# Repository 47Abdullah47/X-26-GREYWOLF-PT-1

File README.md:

<h1 align="center">﷽</h1>
<h1 align="center">
<font size="48"><b>🛦 X-26 GREYWOLF PT-1</b></font>
</h1><br>

<h4 align="center">
  <b>An experimental prototype of <i>X-26 GREYWOLF</i></b>
</h4>
<p align="center">
<a href="#brief interview of the ">Brief interview of The WOLF</a>•
  <a href="#visual looks">Visual Look</a>•
  <a href="#materials list">Materials List</a>•
  <a href="#electronics list">Electronics List</a>•
<a href="#credits">Credits</a>•
<a href="#license">License</a>
</p>
<br>

> **Status:** PT-1 finished  
> **Design:** Fusion 360  
> **Platform:** [Hack Club Blueprint](https://blueprint.hackclub.com/projects/2458) <br>
> **Total Time Spent:** 3+ years <br>
> **Time spent on Blueprint:** 70+ hrs <br>

---<br>

 <br><br>                        
                        
## Brief Interview Of THE WOLF🐺

This WOLF, not a literal one, is the first PT(prototype) of the experimental plane series **GREY WOLF** 
The PT-1 is single engine (not a literal engine could be in future)powered ,running about **1.3-1.5**meters long ,standing almost **30 cm**tall . 
The WOLF has a wingspan of almost **a meter** and a wing area of a **meter** too. Has a total of **8 control surfaces** Two of 'em are flaps,two ailerons ,two stabilators, and two rudders ,not rudders but whole moving tails.Also features three landing gears all of 'em with openning and closing bays.Also in this prototype i've designed my own type of somewhat lookin like S-duct ,Just to study the effects of air in turbulence while flying at low altitudes at high speeds.Expected speeds are like 150-250 mph ,result of edfs 3.4-4kg thrust and planes empty weight being 1.5-2 kgs ,looks a big number but thats a rough guess and the weight can be reduced in real life development.
Abt the electronics , the budget was going very high above 400$ so, i've decided to build them separately.<br>
*Also the .f3d file is very massive upto 150mb's so i've given a google drive link in the **SOURCE FILE*** <a href="Source files">Link to the source file </a>
<br><br>

## Visual Looks

<br><br>
## Materials List
The list of materials used is as follows:-
- **DEPRON** for surface covering and making inner supports maybe.
- **CARBONFIBRE** for making spars,ribs,and frames which are going to handle some aerodynamic stress.
- **PLYWOOD** supplementary material in case of not usin the carbon fibre. maybe i wont use this.
<br><br>
## Electronics List🔌
The list of electronics used are:-
- **Sg-90 Servo** 180 degree rotating servo, for gaining control over control surfaces.
- **80mm Edf**  The power unit thats gonna powerup the whole jet.
- **22.2v 6000mah Lipo**for running these heavy electronics.
- **Small LED lights** for night flight and night landing purpose
***NOTE:-***other electronics and their firmwares are included in their respective repos
<br><br>
**📣AN IMPORTANT NOTICE**<br>
                         Many of the viewers may resemble it with **F-35**or**F-22**, but its not, Its a blend of **F-35,F-22&F-16**
                         u may find some parts similar, but lemme tell u if u look at the intakes they are similar to F-22's ,
                         If u look at the vertical tails and engine u'll find them similar to F-35,And If someone may look at
                         The airframes they are enhanced form of F-16's Air frames.
                         Therefore please do not mix it with Any other Aircraft,I shall be thankful to u.

## Credits💼📜
First of all I'm gonna Credit my **Father** he taught me almost everything about the aircrafts
He's a professional in his feild ,and He is the who encouraged me to build this project..

Secondly My **Big Bro** he was the atual reason i built it ,cuz he challenged me to make my own one
And hes the one who told me about **Blueprint**.So if he wouldnt have challenged me ,my mind  wouldnt have accelerated those ideas that 
led me to design this beast.

Thirdly **Hackclub Blueprint**
I wanna thank the team for starting this type of projects ,that enables many teenagers to enhance thier skills
Also because of **Blueprint** the project that was only a cad file ,is going to come to life.

## License🔐

CC-BY-4.0

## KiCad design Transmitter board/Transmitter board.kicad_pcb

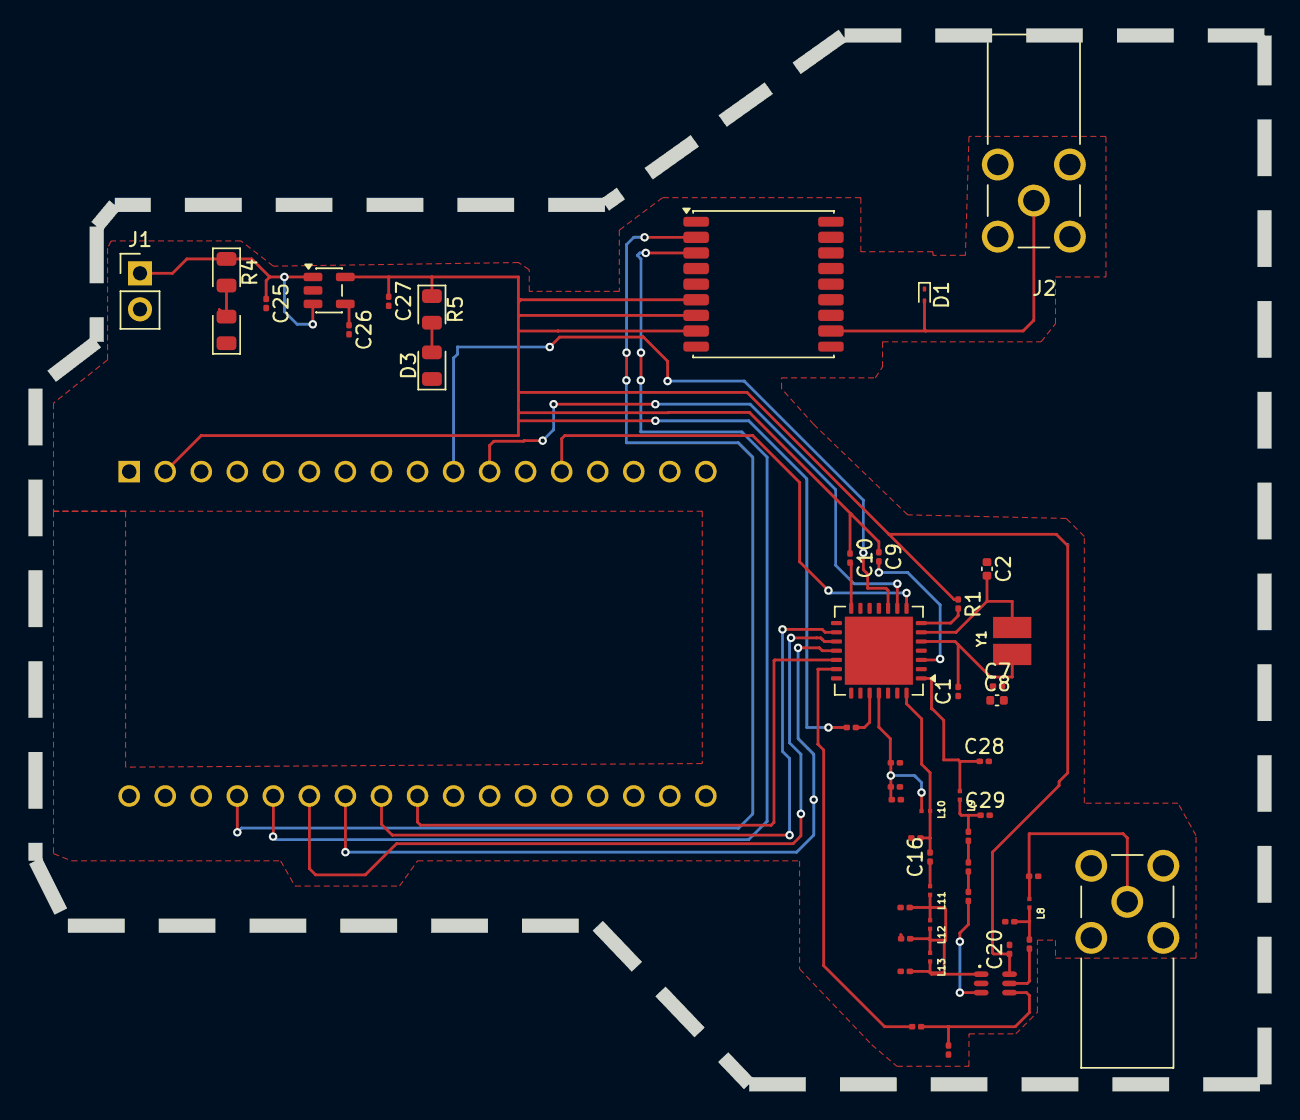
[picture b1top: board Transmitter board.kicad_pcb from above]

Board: 2 copper layers, 86.6 x 73.9 mm, 50 parts (1 on the bottom side), 38 nets.

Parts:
C1, C17, C18: 10pF; C_0201_0603Metric
C2: 10pF; C_0402_1005Metric
C7: 100 n F; C_0201_0603Metric
C8: 100 n F; C_0402_1005Metric
C9, C10, C11: 1u F; C_0201_0603Metric
C12: 3.9pF; C_0201_0603Metric
C13, C14: 6.8pF; C_0201_0603Metric
C15, C19, C29, C30: 1.0pF; C_0201_0603Metric
C16, C31: 100pF; C_0201_0603Metric
C20, C21, C22, C23, C24: 100nF; C_0201_0603Metric
C25: 0.1uF; C_0201_0603Metric
C26: 0.01uF; C_0201_0603Metric
C27: 2.2uF; C_0201_0603Metric
C28: C; C_0201_0603Metric
D1: ESD9B3.3ST5G; D_SOD-923
D2, D3: LED; LED_0805_2012Metric
J1: Conn_01x02; PinHeader_1x02_P2.54mm_Vertical
J2, J3: 85_SMA-50-0-144_111_YH; HUBER_SUHNER_85_SMA-50-0-144_111_YH
L3: PE4259; SOT65P215X110-6N
L8, L9, L12, L13: 6.8nH; IND_LQP03HQ10NH02D
L10: 47nH; IND_LQP03HQ10NH02D
L11: 15nH; IND_LQP03HQ10NH02D
R1: 10 k; R_0201_0603Metric
R2: 0 ohm; R_0201_0603Metric
R3: 10K ohm; R_0201_0603Metric
R4, R5: R; LED_0805_2012Metric
U1: ESP32-DEVKITM-1; MODULE_ESP32-DEVKITM-1
U2: SX1278; QFN-28-1EP_6x6mm_P0.65mm_EP4.8x4.8mm
U3: MAX-M10S; ublox_MAX
U4: TPS79333-EP; SOT-23-5
Y1: NX3225GD-8MHZ-STD-CRA-3; XTAL_NX3225GD-8MHZ-STD-CRA-3

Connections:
/1: C9.1, C10.1, C11.1, C20.1, C27.1, L3.6 (~CTRL/~VDD), R1.1, R5.1, U1.J1_2 (VCC_3V3), U3.6 (V_BCKP), U3.7 (VCC_IO), U3.8 (VCC), U4.5 (OUT)
GND: C1.1, C2.1, C7.2, C8.2, C12.2, C13.2, C14.2, C15.2, C17.2, C18.2, C19.2, C20.2, C21.2, C23.2, C24.1, C25.2, C26.2, C27.2, C28.2, C29.2, D1.1 (A1), D2.1 (K), D3.1 (K), J1.2, J2.G1, J2.G2, J2.G3, J2.G4, J3.G1, J3.G2, J3.G3, J3.G4, L3.2 (GND), U1.J1_1 (GND_J1_1), U1.J3_1 (GND_J3_1), U2.15 (GND), U2.21 (GND), U2.22 (GND), U2.23 (GND), U2.26 (GND), U2.29 (GND), U3.1 (GND), U3.10 (GND), U3.12 (GND), U4.2 (GND)
unnamed: C16.1, L11.1
unnamed: C22.2, L8.2
unnamed: C24.2, J3.1, L8.1
unnamed: C29.1, C30.2, L9.2
unnamed: C30.1, R2.2
unnamed: C31.2, R2.1
unnamed: D1.2 (A2), J2.1, U3.11 (RF_IN)
unnamed: D2.2 (A), R4.2
unnamed: D3.2 (A), R5.2
unnamed: C25.1, J1.1, R4.1, U4.1 (IN), U4.3 (EN)
unnamed: C21.1, L3.4 (CTRL), R3.2
unnamed: C17.1, C18.1, C19.1, L3.1 (RF1), L11.2, L12.1, L12.2, L13.1, L13.2
unnamed: C31.1, L3.3 (RF2)
unnamed: C22.1, L3.5 (RFC)
unnamed: U1.J3_9 (GPIO5), U2.19 (NSS)
unnamed: R1.2, U1.J1_15 (GPIO14), U2.7 (~RESET)
unnamed: U1.J3_8 (GPIO18), U2.16 (SCK)
unnamed: U1.J3_6 (GPIO19), U2.17 (MISO)
unnamed: U1.J3_4 (GPIO21), U3.2 (TXD)
unnamed: U1.J3_5 (GPIO22), U3.3 (RXD)
unnamed: U1.J3_7 (GPIO23), U2.18 (MOSI)
unnamed: U1.J1_13 (GPIO26), U2.8 (DIO0)
unnamed: U1.J1_10 (GPIO32), U2.10 (DIO2)
unnamed: U1.J1_11 (GPIO33), U2.9 (DIO1)
unnamed: C28.1, L9.1, U2.1 (RFI_LF)
unnamed: C15.1, C16.2, L10.1, U2.28 (RFO_LF)
unnamed: R3.1, U2.20 (RXTX/RF_MOD)
unnamed: C9.2, U2.3 (VBAT_ANA)
unnamed: C10.2, U2.14 (VBAT_DIG)
unnamed: C11.2, U2.24 (VBAT_RF)
unnamed: C8.1, U2.2 (VR_ANA)
unnamed: C7.1, U2.4 (VR_DIG)
unnamed: C12.1, C13.1, C14.1, L10.2, U2.25 (VR_PA)
unnamed: C1.2, U2.5 (XTA), Y1.1
unnamed: C2.2, U2.6 (XTB), Y1.2
unnamed: C26.1, U4.4 (BP)

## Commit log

2026-01-25 Modify Bill(BOM).csv with new product details
    Updated Bill(BOM).csv with new item entries and pricing.
2026-02-11 Update BOM with new items and costs
2026-02-18 Fix duplicate entries in README
    Removed duplicate platform and time spent information.
2026-03-03 Create Source files (google drive link)
2026-03-03 Add project repository link
2026-03-05 Update README with electronics note and design clarification
    Added a note about included electronics and clarified design similarities.
2026-03-05 Update README.md for clarity and formatting
    Fixed formatting issues and improved readability.
2026-03-05 Add link to source file in README
    Updated README to include a link to the source file for the .f3d file.
2026-03-05 Update project link from GitHub to Google Drive
2026-03-05 Fix link text for source file in README
2026-03-05 Update README with more visual screenshots
    Added additional screenshots to the Visual Looks section.
2026-03-05 Fix spelling errors and enhance README clarity
    Corrected spelling errors and improved clarity in the README.
